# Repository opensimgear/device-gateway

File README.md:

# OpenSimGear device-gateway

## Development status and disclaimer

This project is heavily under development and is not ready for use. Use it entirely at your own risk. To the fullest extent permitted by applicable law, the authors and contributors disclaim all liability for any damage, loss, or other issues arising from its use.

STM32G0B1 USB-to-CAN FD gateway with **USB-C, two parallel 4P4C powered CAN sockets, and a centre-positive 5.5 × 2.1 mm 12 V power socket**. The two CAN sockets continue one linear bus; they are not separate controller channels. The gateway can sit at either end or in the middle of the chain.

## Implemented prototype

- C firmware for `gateway_g0b1cb_v0_1_0`, with USB HID and CDC, a unique MCU-derived USB serial, and active CAN FD at 500 kbit/s arbitration / 2 Mbit/s data.
- Automatic discovery, enrollment and logical route allocation for up to 32 remembered module identities. New input identities append to a persistent ordered controller list; output-only identities retain guarded routes without a HID collection or report ID; enabled offline devices keep neutral HID collections.
- One HID interface with a joystick top-level collection and stable report ID for each enabled module. Each profile supports up to eight 16-bit axes, four hats and 128 buttons. Host/game interpretation of multiple collections still needs physical testing.
- Bounded CAN queues, sequence/lease checks, direct USB input ownership, 250 ms input timeout, 1.5 s presence timeout, and bus-off recovery.
- CRC-protected device visibility and controller order stored in two independent flash pages with a commit marker written last. Automatic batched activation saves an exact generation before USB reconnects; explicit Disable/Enable/Remove retain or forget identities as requested.
- Editable KiCad schematic, PCB, exact-part BOM, local libraries, review and fabrication exports, and a Linux SocketCAN reference peer.

The generic device and gateway now share **Cyphal/CAN**, using generated OpenSimGear
DSDL types and the actual libcanard 5.0 transport. Standard Heartbeat and GetInfo,
CAN node-ID autoconfiguration, transfer-ID deduplication and multi-frame reassembly
run in both firmwares. CAN addresses are separate from the gateway's 32 logical
routes, persistent descriptor order and explicit report IDs. Input acknowledgements still follow actual USB
HID completion. The prior private CAN FD v1/v2 frames are incompatible and rejected.

Cockpit desktop uses the correlated CDC v3 adapter with `canProtocol=3`.

Send `panel-stream\n` on an open CDC connection to opt into unsolicited panel
records. Each record is a complete JSON line between command replies. The
first record has `panelStream: "reset"`. Event records have
`panelStream: "event"`, the module's `moduleId`, its physical `sourceNode`, and
a hexadecimal `payload` containing the Cyphal subject 2007 application bytes.
Wait for a layout and a complete state before applying edges. A
`panelStream: "loss"` record withdraws the named module's state. A reset
withdraws all stream state and can also occur on local queue overflow or
expiration. A new CDC connection requires a new opt-in.
Enrollment runs in the gateway with Cockpit closed. Enabled devices remain neutral
controllers while temporarily offline and appear ghosted in Cockpit. Disable
removes a Windows HID collection while remembering the device and its disabled
choice; repeated announcements and reboot never undo it. Enable appends at the
end. Remove forgets an offline identity; rediscovery enrolls it as new. Removing
published collections warns that remaining game bindings may need updating.

USB exposes only enabled controllers, including their retained offline ghosts.
There is no permanent management collection or unused joystick placeholder;
zero enabled controllers means CDC-only enumeration. Existing controller order,
report IDs and input definitions survive automatic additions, but Windows/game
binding continuity still requires physical qualification, especially transitions
between one and multiple collections. Software resource bounds are explicit,
and excess announcements produce visible capacity diagnostics. Direct device
USB ownership leaves gateway input neutral. The [Pico debug gateway](simulation/pico/README.md)
reuses current gateway/device contracts for eight virtual devices, Cockpit input
controls, physical USB HID, persistent settings and DCS-BIOS panel testing. Older
protocol-1 Pico images retain their compatibility adapter.

Cockpit can claim a module configuration draft, change input mappings/calibration,
and apply or persist its settings over the current identity/session/lease-bound
CAN route. Enabled HID profiles remain frozen until an explicit update-profile
operation; disabled devices remain configurable. Native behavior/journal tests,
actual transport integration, independent gateway/device acceptance and the
STM32 cross-build validate source behavior. Physical USB/CAN acceptance remains
pending. See the [architecture record](https://github.com/opensimgear/opensimgear.github.io/blob/main/src/content/docs/gear/architecture/usb-hid.md)
and [GitHub project](https://github.com/orgs/opensimgear/projects/2).

Cockpit also discovers and invokes device-advertised actions through the guarded
CDC/CAN route. Descriptions, invocations and readable state reuse bounded request/reply
fragments, with separate action dispatch and `targetAction` results. Actions remain
reachable on online disabled controllers and direct-USB input owners after current
lease status arrives. LED setters are volatile and do not claim settings, write flash
or change HID descriptors. The gateway forwards action catalogues without retaining
them in registry storage. Per-endpoint claims/renewal/owned invocation/release
use these same routes and prevent competing clients at the device. Independent
device expiry or route loss applies its validated fallback; tokens remain private.
Output-only modules enroll with `outputOnly:true` and `reportId:null`; Enable
returns `input_not_supported`. Unchanged descriptors activate without USB
reconnection. See the [ownership contract](https://github.com/opensimgear/protocol/blob/main/serial/output-ownership.md). See [milestone 1](https://github.com/opensimgear/cockpit/issues/13)
and the [action contract](https://github.com/opensimgear/protocol/blob/main/serial/device-actions.md).

The same guarded request/reply transport also carries `events state` and
`events read <stream> <after>`, returning request-scoped `targetEvents` JSON.
Devices retain ordered debounced button/encoder transitions in their own bounded
log; the gateway forwards pages independently of HID enablement or direct USB
ownership. Consumers baseline before forwarding new presses and recover from
explicit stream/gap errors. See the [panel event contract](https://github.com/opensimgear/protocol/blob/main/serial/panel-input-events.md).

Radio panels reuse these same routes: display actions declare fitted geometry and
encoding, and event snapshots add maintained/selector metadata plus independent
calibrated axes and availability. The gateway forwards these bounded JSON fields
without storing output state or inferring it from HID. The starter has no fitted
display; native radio frequency/preset/text ports execute the same product callbacks
that a physical display driver supplies. See the [radio simulation](https://github.com/opensimgear/device-template/blob/main/simulation/configs/radio-panel.json).

## Independent simulation

From this repository, launch the native gateway:

```sh
python3 simulation/run.py --identity 0123456789abcdef01234567
```

Start Cockpit normally, then start two or three device processes from
[device-template/simulation](https://github.com/opensimgear/device-template/tree/main/simulation),
using the same gateway identity and separate JSON definitions. Devices may start
before or after the gateway. Cockpit discovers the ordinary gateway endpoint;
it does not start or configure simulation processes. The gateway owns discovery,
automatic enrollment, configuration forwarding and dynamic HID reports. Closing Cockpit
leaves the processes running. See [the simulation guide](simulation/README.md)
for state, diagnostics and the optional [Pico implementation](simulation/pico/README.md).

Run integration tests from this repository alone:

```sh
python3 tests/e2e/run.py --sanitize
python3 tests/e2e/run.py --sanitize --with-cockpit
```

The runner clones and initializes required repositories, builds their components,
and tests three independently configured devices. `--with-cockpit` also clones
Cockpit and tests its normal Rust adapters. Everything stays under this repository’s
ignored `.e2e/`; no sibling checkout or parent workspace setup is required. See the
[E2E guide](tests/e2e/README.md) for source revisions and local development overrides.
Standalone simulation builds and state stay in `.simulation/`.

The native simulation generates production HID descriptors and input reports,
with HID delivery completed inside the process. It does not publish devices to
the host operating system, so simulated controllers do not appear in `hidutil list`.

## Connectors and power

Both sockets use the same four contacts, numbered by the selected manufacturer's drawing:

| Contact | Signal            |
| ------- | ----------------- |
| 1       | Protected BUS_12V |
| 2       | CAN_H             |
| 3       | CAN_L             |
| 4       | GND               |

Use continuity-checked straight-through wiring with CAN_H/L on a qualified twisted pair. Ordinary reversed or coiled handset cords are not qualified CAN cables. Put 120 Ω across contacts 2/3 in a removable endpoint plug at each physical end of the chain; an inline gateway has no termination. A 4P4C jack is commonly called RJ9/RJ10/RJ22 rather than RJ11. This connector choice follows the requested four-position, four-contact standard.

One regulated external 12 V supply feeds each chain through protected gateway injection. USB powers the local gateway electronics and does not energize the chain. The provisional bench budget is **250 mA total for the gateway's 12 V branch and all modules**, at 20–40 °C, with a supply current limit of 0.5 A. The PCB's resettable fuse is not a precision current limiter. Cable resistance, thermal behaviour, short-circuit protection and hot-plug behaviour require measurement. The 32-identity software bound does not establish a 32-module power allowance.

Use one gateway per CAN/power chain. Multiple gateways connect independently to the host by USB; do not join their CAN or powered trunks. CAN and power pass-through are passive and continue through local MCU reset. Historical six-contact module boards have a different pinout and are incompatible with the new four-contact standard.

## Build and review

From `firmware/`, run the native checks without downloading dependencies:

```sh
cmake --preset native
cmake --build --preset native
ctest --preset native
```

For the embedded build, put Arm GNU Embedded tools on PATH and supply USB identifiers you are authorized to use:

```sh
cmake --preset gateway -DOSG_USB_VID=<your-VID> -DOSG_USB_PID=<your-PID>
cmake --build --preset gateway
```

ELF, BIN, HEX and MAP outputs are placed under `.build/gateway/`. No command flashes hardware automatically. See the [firmware guide](firmware/README.md) for exact dependency pins, SWD flashing, recovery and CDC commands. See [CAN peer testing](tools/README.md) for an executable matching module peer.

- [PCB project, pin map and BOM](electronics/boards/gateway/0.1.0/README.md)
- [Fabrication construction](electronics/boards/gateway/0.1.0/FABRICATION.md)
- [Electrical/static validation](electronics/boards/gateway/0.1.0/VALIDATION.md)
- [Firmware validation results](firmware/VALIDATION.md)
- [CAN application framing](firmware/docs/cyphal.md)
- [Registration, HID layout and storage semantics](firmware/docs/core.md)
- [Assembly and enclosure constraints](hardware/README.md)

Static checks and cross-compilation establish source-level behaviour. No gateway PCB has been assembled, flashed or electrically measured; fabrication review and physical USB/CAN/power acceptance remain required. The initial network validation target is up to ten modules and 5 m total cable with typical links below 1 m, subject to the power budget established by measurement.

## Related repositories and licensing

[Protocol](https://github.com/opensimgear/protocol), [firmware-common](https://github.com/opensimgear/firmware-common), [device-template](https://github.com/opensimgear/device-template), [Cockpit](https://github.com/opensimgear/cockpit), and the [website](https://github.com/opensimgear/opensimgear.github.io) own their respective shared definitions and implementations. This gateway uses pinned common firmware dependencies; a checked-in shared Cyphal snapshot tracks the canonical protocol repository.

Copyright © Ivan Gregurić Ortolan. All rights reserved for original OpenSimGear material while licensing is under review. The [temporary licensing policy](LICENSE) defines the current scope for firmware, electronics and other original material. Creative external contributions are suspended during review; [CONTRIBUTING.md](CONTRIBUTING.md) explains the policy for factual bug reports and questions. Included KiCad library data retains its [upstream license](electronics/boards/gateway/0.1.0/LICENSE-KICAD.md), and firmware dependencies retain their upstream licenses and notices. No public USB VID/PID allocation is claimed.

PCB version **0.1.0** stays fixed while pre-live; see [PCB versioning](electronics/VERSIONING.md).

## JLCPCB exports

From this repository root, run `sh tools/bundle-jlcpcb.sh` for the latest numeric board version, or `sh tools/bundle-jlcpcb.sh 0.1.0` for a specific version. Requires KiCad 10 (`kicad-cli`) and Python 3. The script generates a Gerber ZIP plus separate JLCPCB BOM/CPL CSVs in the workspace `.research/jlcpcb/` directory. Use `--output-dir path` to change the destination or `--smd-only` to omit through-hole assembly. See [tool usage](tools/README.md) and the board’s fabrication notes before ordering.

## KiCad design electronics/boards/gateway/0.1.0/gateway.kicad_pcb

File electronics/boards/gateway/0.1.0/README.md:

# Gateway v0.1.0

## Development status and disclaimer

This project is heavily under development and is not ready for use. Use it entirely at your own risk. To the fullest extent permitted by applicable law, the authors and contributors disclaim all liability for any damage, loss, or other issues arising from its use.

Open `gateway.kicad_pro` in **KiCad 10**. This revision develops the gateway around the reviewed STM32G0B1 starter core, adding protected 12 V injection and two physical **4P4C** modular CAN/power sockets. The board is a prototype; no assembly has been measured or fabricated. [Validation](VALIDATION.md) records actual static results and validation limits. [Fabrication](FABRICATION.md), [footprint review](FOOTPRINTS.md), [BOM](bom.csv), [schematic](review/schematic.pdf) and [copper preview](review/pcb.svg) and [1:1 assembly drawings](review/assembly.pdf) accompany the editable CAD.

The connectors are four-position/four-contact jacks, often sold as RJ9/RJ10/RJ22 handset connectors. They are smaller than six-position RJ11/RJ12 sockets. They implement the user's final **4P4C everywhere** requirement. These powered sockets must never connect to telephone equipment. The former six-contact template ecosystem must be migrated before connecting a module; adapters or casual telephone-cord substitutions are not assumed safe.

| Socket / header | Contacts |
| --- | --- |
| J1 USB-C | USB 2.0 device, external 5.1 kΩ Rd on CC1/CC2, no USB PD |
| J2/J3 powered CAN | 1 protected BUS_12V; 2 CAN_H; 3 CAN_L; 4 GND |
| J5 12 V barrel | 5.5 mm OD / 2.1 mm ID mating plug, center positive; sleeve GND; switched sleeve unused |
| J4 SWD | 1 target 3.3 V reference, 2 GND, 3 SWDIO, 4 SWCLK, 5 NRST |
| J6 CAN test | 1 CAN_H, 2 CAN_L, 3 GND; no power output |

Contact numbering comes from the exact manufacturer's drawing and local footprint; see [FOOTPRINTS.md](FOOTPRINTS.md). Qualify a straight-through four-conductor cable whose center pair carries CAN_H/L as a twisted pair. Most handset cords reverse contacts end to end and many are flat, untwisted cable. A reversed cord swaps both power polarity and CAN polarity. Use continuity checks at every contact before energizing any new cable. No hot-plug or cable-current qualification has been established.

J2 and J3 are electrically parallel on a single CAN FD segment. Copper passes CAN and protected trunk power through independently of MCU reset or firmware. Use a linear chain. Fit a removable **120 Ω, 1%, ≥0.25 W** resistor between contacts **2 and 3 only** inside an endpoint plug in the unused gateway port, and a second endpoint plug in the final module's unused port. Remove termination on every intermediate module. There is no permanent PCB terminator; J6 is a bench test connection. Do not form a ring.

The barrel input feeds F2 (350 mA hold / 750 mA trip, 30 V PPTC), D6 SS14 reverse-polarity diode, then D7 SMBJ15A TVS at BUS_12V. Both jacks and the MCU branch receive this protected voltage. F1 (200 mA hold / 30 V) separately protects the MCU branch, followed by D1, the local D5 TVS and RECOM 5 V converter. U6/U7 LM66100 combine regulated bus power and USB VBUS into SYS_5V with TI's Figure 17 continuous-output priority topology: the buck-side status output drives USB-side enable through OR_STATUS, with R6 pulling up to BUCK_5V, followed by the 3.3 V LDO. USB never has a path that generates 12 V. The power-source selection is passive and independent of firmware; leakage, backfeed and source transitions still require measurement. Use one 12 V source per trunk; do not join independently powered gateways.

Use a **current-limited regulated 12 V bench supply, set ≤0.5 A**, and provisionally budget **≤250 mA total** at the barrel input at 20–40°C, including the gateway and all chain devices. The connector's 1.5 A/contact rating does not establish a cable/system current budget. F2's hold rating derates with temperature (300 mA at 40°C and 150 mA at 85°C); a PPTC is a slow fault element, not an accurate electronic current limiter. This prototype has no sustained-overvoltage cutoff. TVS and fuse behaviour under actual faults, wire heating, diode drop and connector temperature must be qualified before extending these limits.

| Firmware signal | MCU pad | LQFP48 pin |
| --- | --- | --- |
| USB D− / D+ | PA11 / PA12 | 33 / 34 |
| USB VBUS presence | PB0, 10 kΩ / 15 kΩ divider | 19 |
| CAN RX / TX | PB8 / PB9, AF3 | 47 / 48 |
| CAN standby, high = standby | PB5, external 10 kΩ pull-up | 44 |
| LED, active high through 1 kΩ | PA5 | 16 |
| SWDIO / SWCLK | PA13 / PA14 | 35 / 36 |
| Reset | PF2-NRST | 10 |

Clocks use internal oscillators. VDD, VDDA, VREF+ and VBAT use 3.3 V; the LQFP48 package internally connects USB supply to VDD. Leave PA11/PA12 remapping disabled and disable UCPD dead-battery pull-downs on unused PA9/PA10. The transceiver is in standby during reset; CAN traffic and chain power continue through the passive connectors. External control headers from the device template are absent.

The four-layer board retains the 65 × 55 mm outline and reviewed USB geometry: 0.2474 mm main track width / 0.1501 mm pair gap above a continuous L2 reference plane. Request the documented JLC04161H-7628 construction, 90 Ω differential ±10%, final geometry approval and coupon/TDR; the calculation is not a measured impedance. See [fabrication instructions](FABRICATION.md). Reproduce static checks and exports with `sh tools/check-and-export.sh 0.1.0` from the repository root after every CAD edit.

`KiCad.kicad_sym` / `KiCad.pretty` retain selected upstream library entries under [KiCad's license](LICENSE-KICAD.md). `OpenSimGear` contains local manufacturer-derived connector, PPTC and other reviewed footprints. Upstream 3D paths require KiCad's model installation; newly authored parts deliberately omit unverified models.

Follow [PCB versioning](../../../VERSIONING.md): this single current design is version **0.1.0**, held fixed until launch.

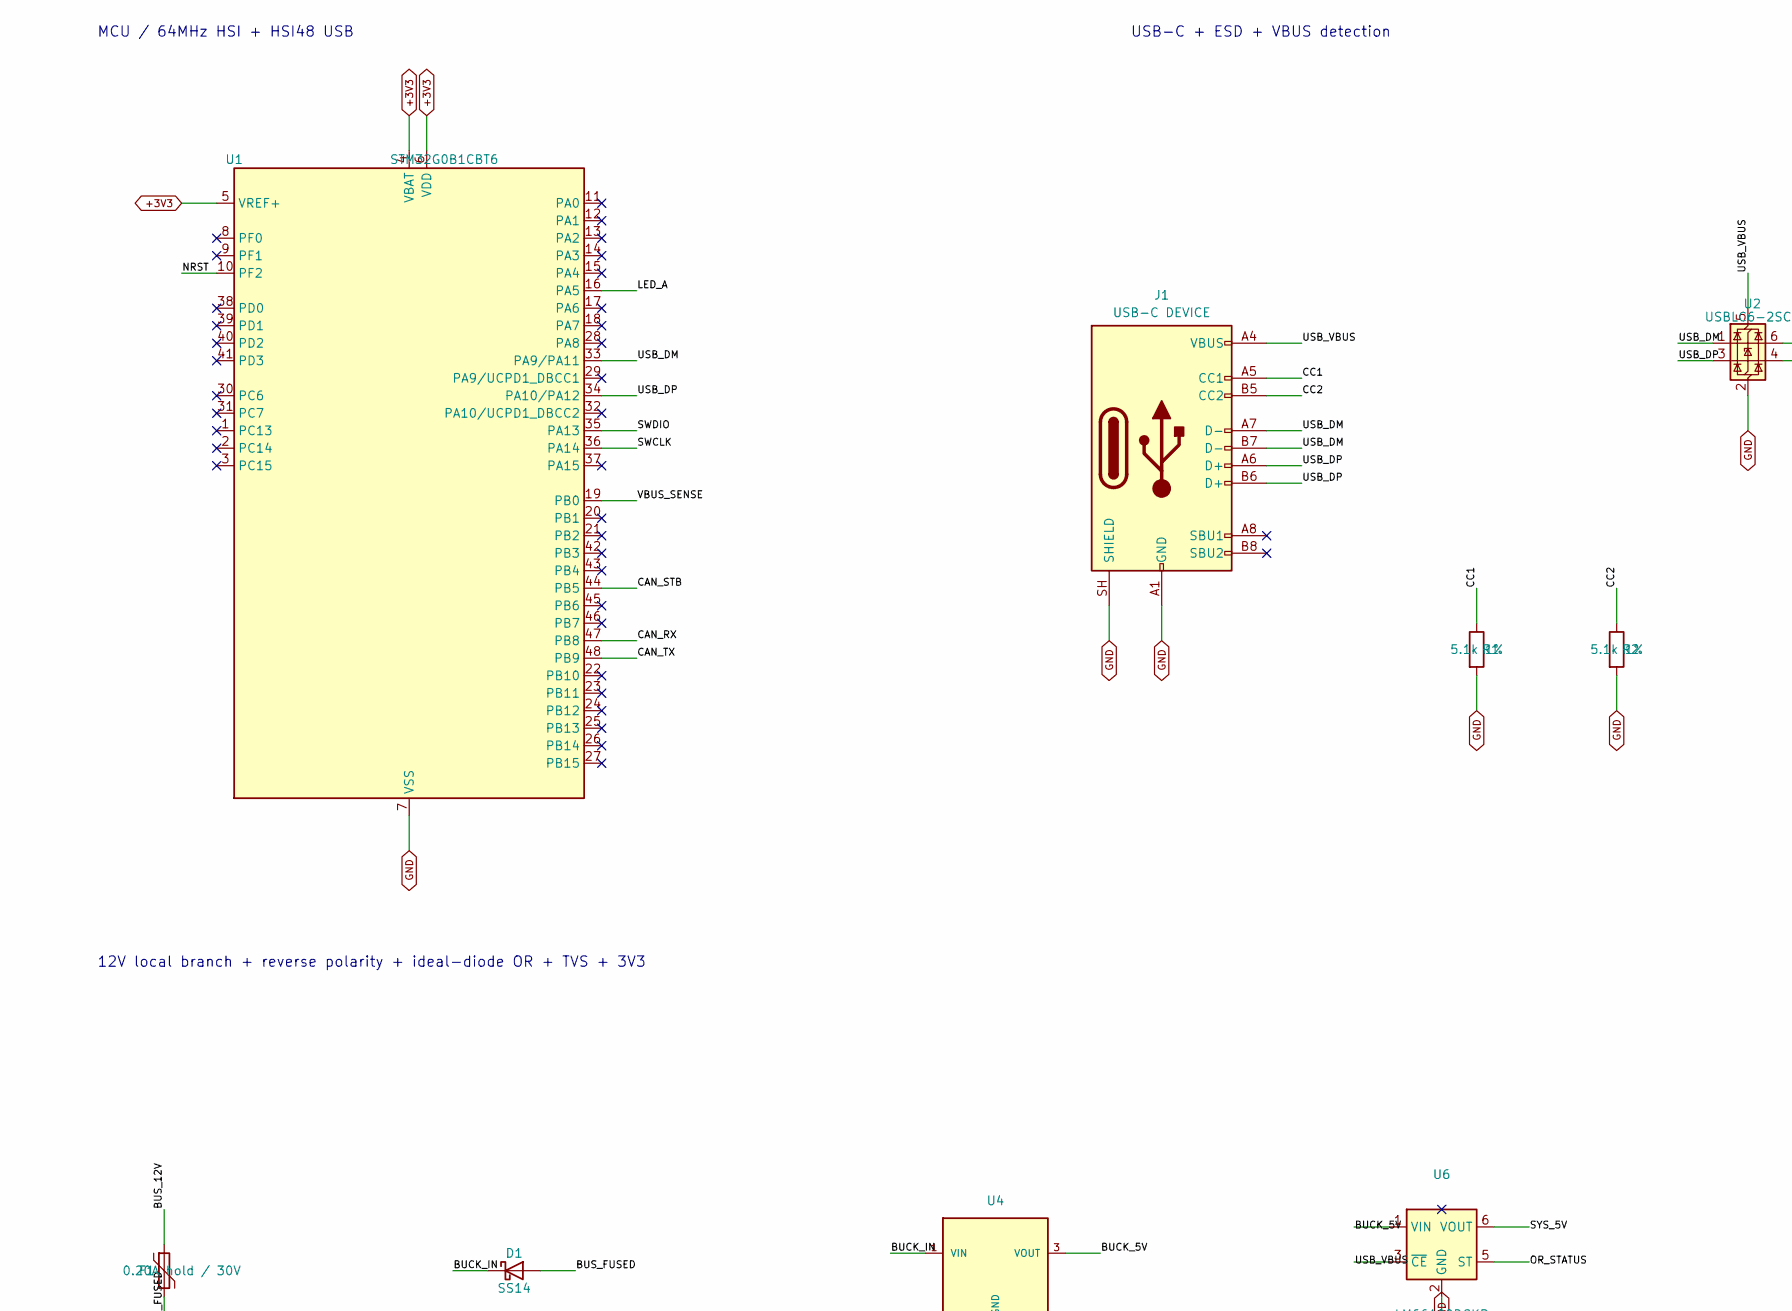
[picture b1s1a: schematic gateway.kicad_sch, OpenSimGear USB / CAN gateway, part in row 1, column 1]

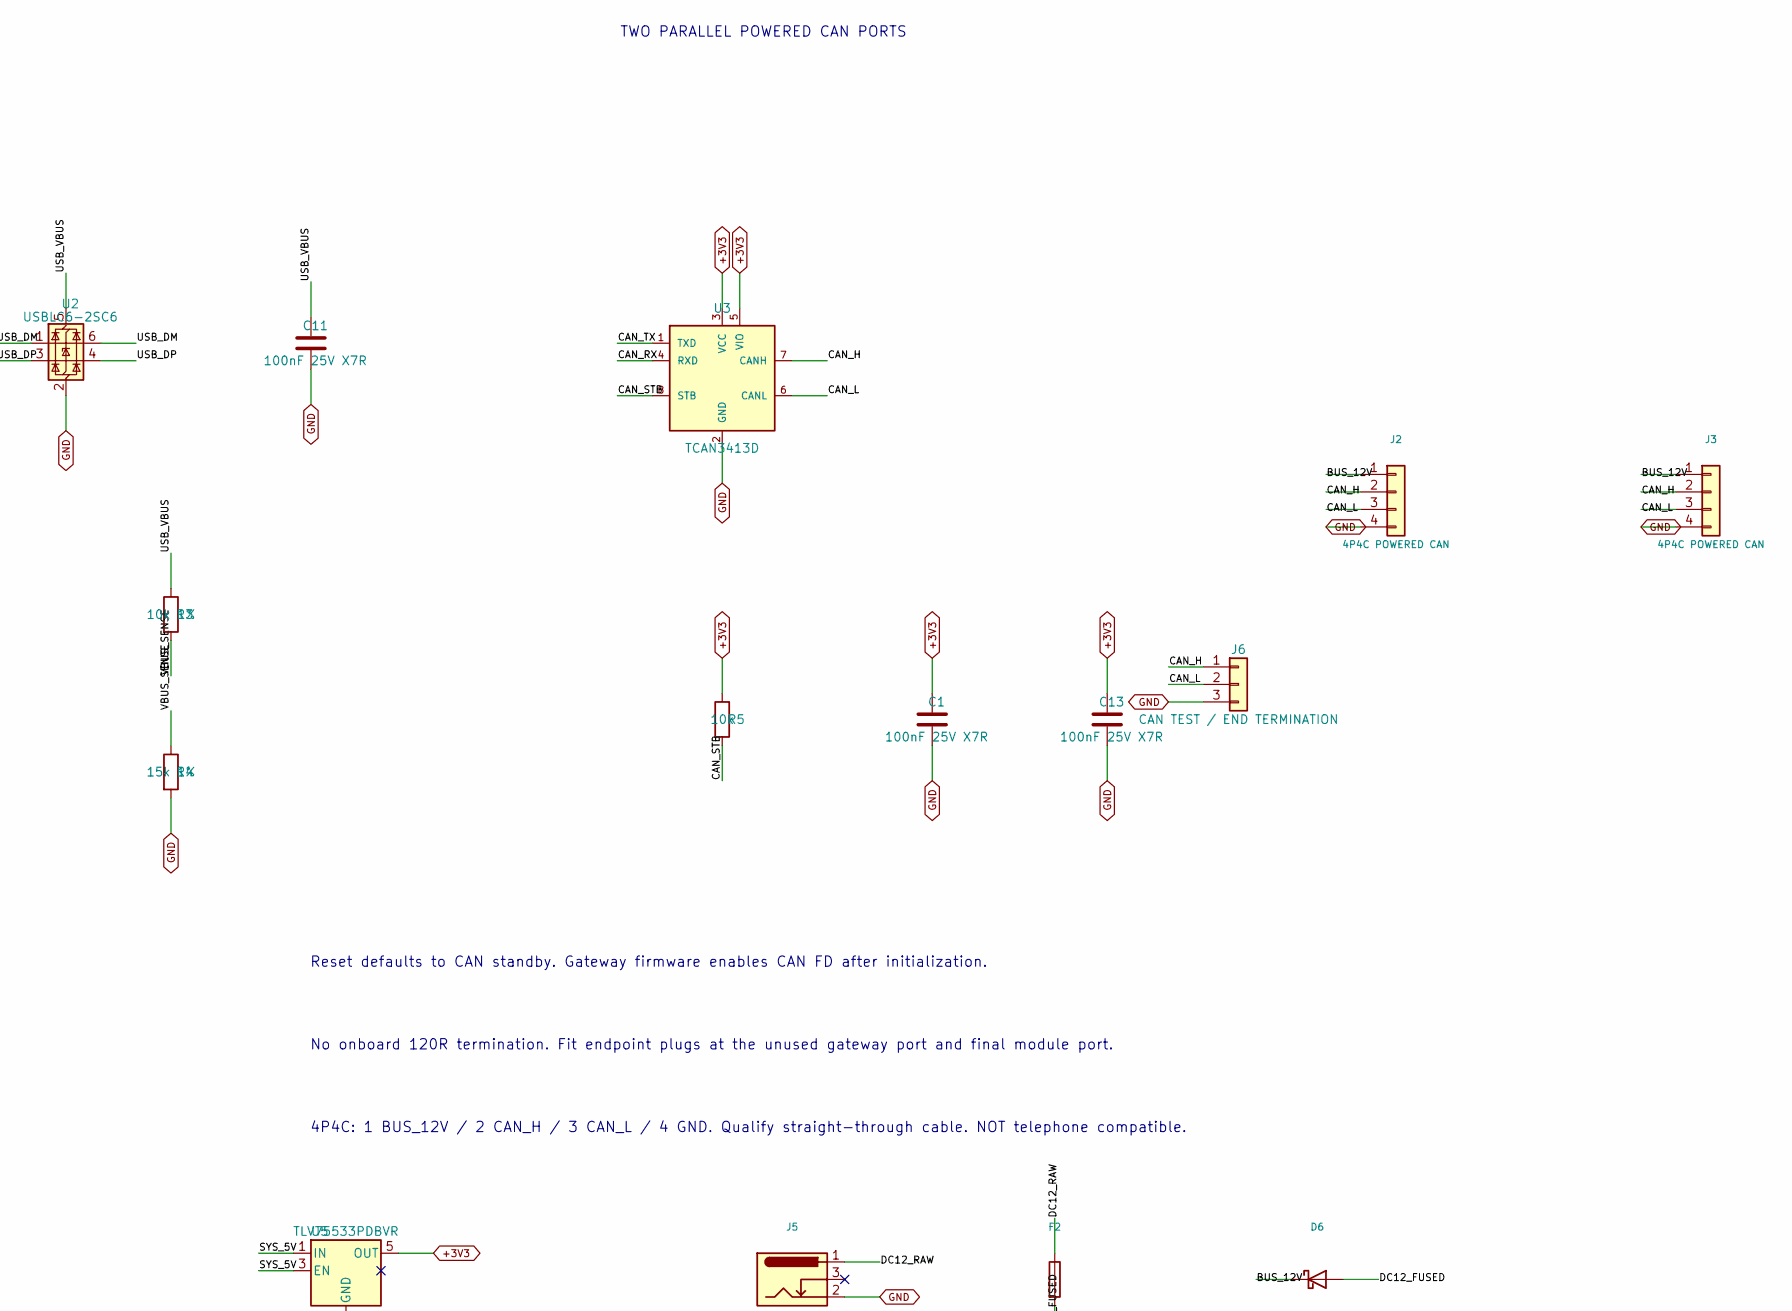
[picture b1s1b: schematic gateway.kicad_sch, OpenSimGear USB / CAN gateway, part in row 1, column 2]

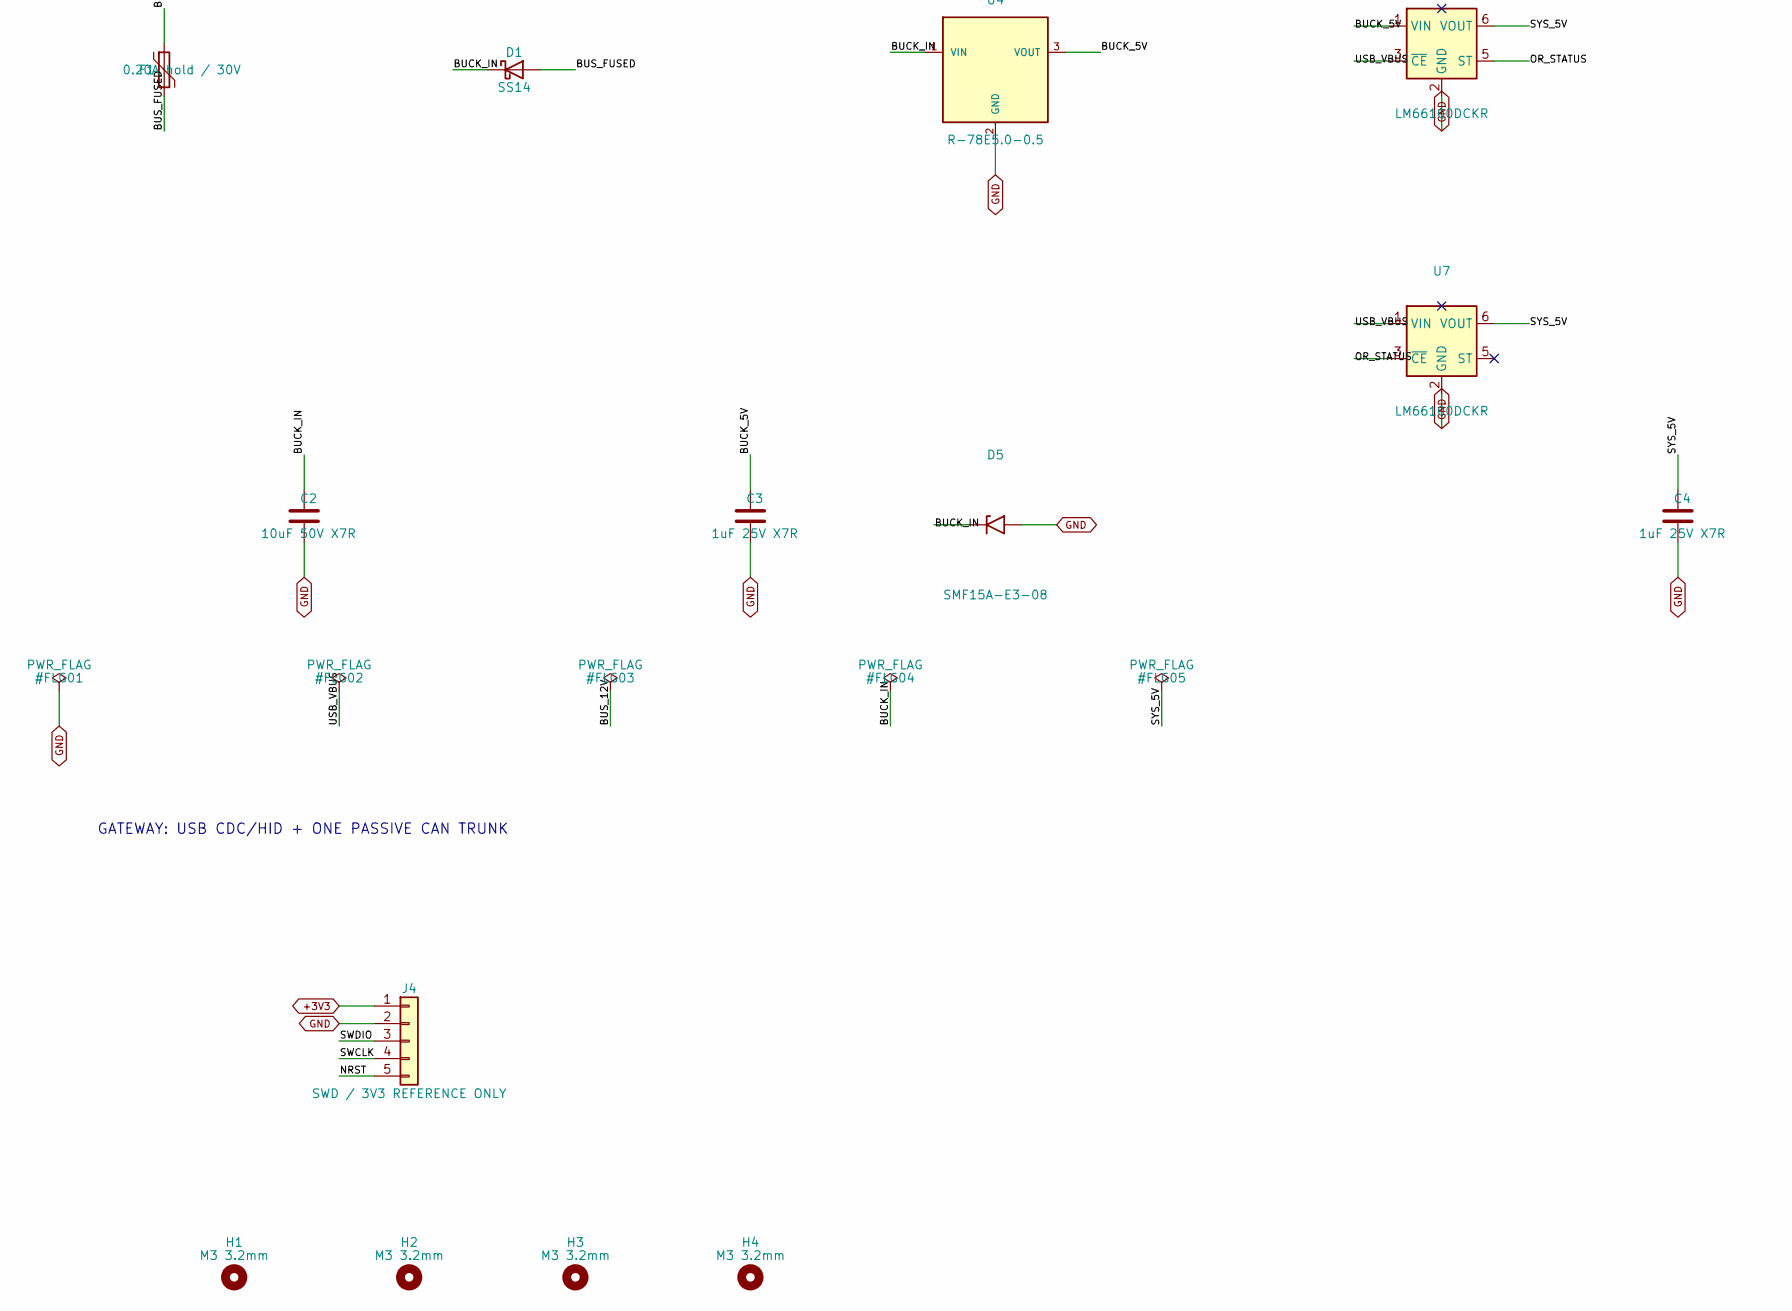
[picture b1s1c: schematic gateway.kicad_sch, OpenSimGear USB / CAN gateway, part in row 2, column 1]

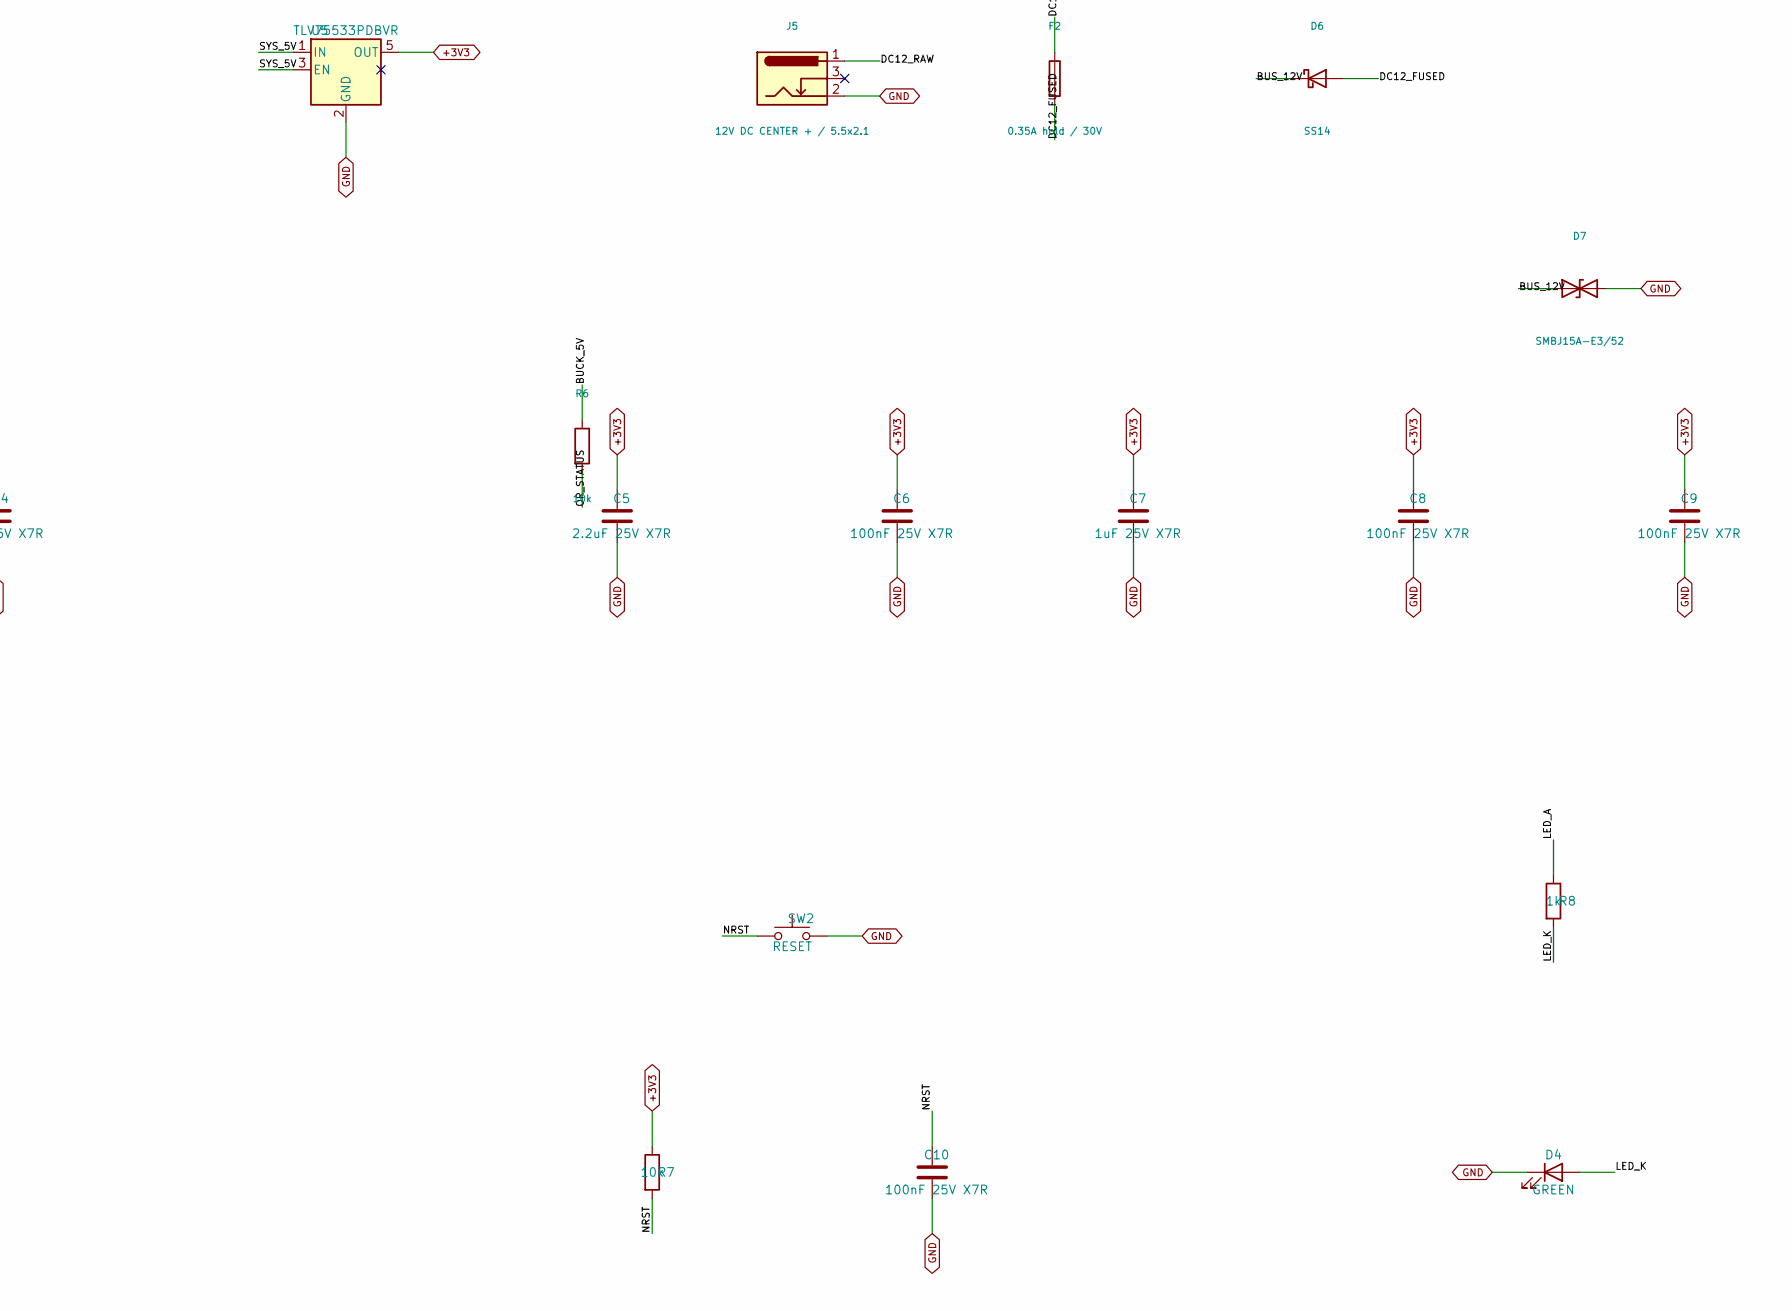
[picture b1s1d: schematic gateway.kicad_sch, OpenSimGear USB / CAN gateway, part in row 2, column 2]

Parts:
C1, C6, C8, C9, C10, C11, C13: 100nF 25V X7R; C_0805_2012Metric; MPN C0805C104K3RACTU
C2: 10uF 50V X7R; C_1210_3225Metric; MPN GRM32ER71H106KA12L
C3, C4, C7: 1uF 25V X7R; C_0805_2012Metric; MPN C2012X7R1E105K125AB
C5: 2.2uF 25V X7R; C_0805_2012Metric; MPN C2012X7R1E225K125AB
D1, D6: SS14; D_SMA; MPN SS14-E3/61T
D4: GREEN; LED_Kingbright_AP2012SGC_0805; MPN AP2012SGC
D5: SMF15A-E3-08; D_SMF; MPN SMF15A-E3-08
D7: SMBJ15A-E3/52; D_SMB; MPN SMBJ15A-E3/52
F1: 0.20A hold / 30V; Fuse_Littelfuse_1206L020-30YR; MPN 1206L020/30YR
F2: 0.35A hold / 30V; Fuse_Littelfuse_1206L035-30WR; MPN 1206L035/30WR
H1, H2, H3, H4: M3 3.2mm; MountingHole_3.2mm_M3
J1: USB-C DEVICE; USB_C_Receptacle_GCT_USB4105-xx-A_16P_TopMnt_Horizontal; MPN USB4105-GF-A
J2, J3: 4P4C POWERED CAN; RJ4P4C_Evercom_5301-4P4C_Horizontal; MPN 5301-4P4C
J4: SWD / 3V3 REFERENCE ONLY; PinHeader_Samtec_TSW-105-07-L-S_P2.54mm_Vertical; MPN TSW-105-07-L-S
J5: 12V DC CENTER + / 5.5x2.1; BarrelJack_SameSky_PJ-102AH_Horizontal; MPN PJ-102AH
J6: CAN TEST / END TERMINATION; PinHeader_Samtec_TSW-103-07-L-S_P2.54mm_Vertical; MPN TSW-103-07-L-S
R1, R2: 5.1k 1%; R_0805_2012Metric; MPN RC0805FR-075K1L
R3: 10k 1%; R_0805_2012Metric; MPN RC0805FR-0710KL
R4: 15k 1%; R_0805_2012Metric; MPN RC0805FR-0715KL
R5, R6, R7: 10k; R_0805_2012Metric; MPN RC0805FR-0710KL
R8: 1k; R_0805_2012Metric; MPN RC0805FR-071KL
SW2: RESET; SW_PUSH_6mm_H4.3mm; MPN B3F-1002-G
U1: STM32G0B1CBT6; LQFP-48_7x7mm_P0.5mm; MPN STM32G0B1CBT6
U2: USBLC6-2SC6; SOT-23-6; MPN USBLC6-2SC6
U3: TCAN3413D; SOIC-8_3.9x4.9mm_P1.27mm; MPN TCAN3413D
U4: R-78E5.0-0.5; Converter_DCDC_RECOM_R-78E-0.5_THT; MPN R-78E5.0-0.5
U5: TLV75533PDBVR; SOT-23-5; MPN TLV75533PDBVR
U6, U7: LM66100DCKR; TI_DCK0006A_SC70-6_LM66100; MPN LM66100DCKR

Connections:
+3V3: C1.1, C5.1, C6.1, C7.1, C8.1, C9.1, C13.1, J4.1, R5.1, R7.1, U1.4 (VBAT), U1.5 (VREF+), U1.6 (VDD), U3.3 (VCC), U3.5 (VIO), U5.5 (OUT)
/BUCK_5V: C3.1, R6.1, U4.3 (VOUT), U6.1 (VIN)
/BUCK_IN: C2.1, D1.1 (K), D5.1 (A1), U4.1 (VIN)
/BUS_12V: D6.1 (K), D7.1 (A1), F1.1, J2.1, J3.1
/BUS_FUSED: D1.2 (A), F1.2
/CAN_H: J2.2, J3.2, J6.1, U3.7 (CANH)
/CAN_L: J2.3, J3.3, J6.2, U3.6 (CANL)
/CAN_RX: U1.47 (PB8), U3.4 (RXD)
/CAN_STB: R5.2, U1.44 (PB5), U3.8 (STB)
/CAN_TX: U1.48 (PB9), U3.1 (TXD)
/CC1: J1.A5 (CC1), R1.1
/CC2: J1.B5 (CC2), R2.1
/DC12_FUSED: D6.2 (A), F2.2
/DC12_RAW: F2.1, J5.1
/LED_A: R8.1, U1.16 (PA5)
/LED_K: D4.2 (A), R8.2
/NRST: C10.1, J4.5, R7.2, SW2.1, U1.10 (PF2)
/OR_STATUS: R6.2, U6.5 (ST), U7.3 (~CE)
/SWCLK: J4.4, U1.36 (PA14)
/SWDIO: J4.3, U1.35 (PA13)
/SYS_5V: C4.1, U5.1 (IN), U5.3 (EN), U6.6 (VOUT), U7.6 (VOUT)
/USB_DM: J1.A7 (D-), J1.B7 (D-), U1.33 (PA9/PA11), U2.1 (I/O1), U2.6 (I/O1)
/USB_DP: J1.A6 (D+), J1.B6 (D+), U1.34 (PA10/PA12), U2.3 (I/O2), U2.4 (I/O2)
/USB_VBUS: C11.1, J1.A4 (VBUS), J1.A9 (VBUS), J1.B4 (VBUS), J1.B9 (VBUS), R3.1, U2.5 (VBUS), U6.3 (~CE), U7.1 (VIN)
/VBUS_SENSE: R3.2, R4.1, U1.19 (PB0)
GND: C1.2, C2.2, C3.2, C4.2, C5.2, C6.2, C7.2, C8.2, C9.2, C10.2, C11.2, C13.2, D4.1 (K), D5.2 (A2), D7.2 (A2), J1.A1 (GND), J1.A12 (GND), J1.B1 (GND), J1.B12 (GND), J1.SH (SHIELD), J2.4, J3.4, J4.2, J5.2, J6.3, R1.2, R2.2, R4.2, SW2.2, U1.7 (VSS), U2.2 (GND), U3.2 (GND), U4.2 (GND), U5.2 (GND), U6.2 (GND), U7.2 (GND)

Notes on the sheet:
12V local branch + reverse polarity + ideal-diode OR + TVS + 3V3
No onboard 120R termination. Fit endpoint plugs at the unused gateway port and final module port.
MCU / 64MHz HSI + HSI48 USB
TWO PARALLEL POWERED CAN PORTS
4P4C: 1 BUS_12V / 2 CAN_H / 3 CAN_L / 4 GND. Qualify straight-through cable. NOT telephone compatible.
Reset defaults to CAN standby. Gateway firmware enables CAN FD after initialization.
USB-C + ESD + VBUS detection
GATEWAY: USB CDC/HID + ONE PASSIVE CAN TRUNK

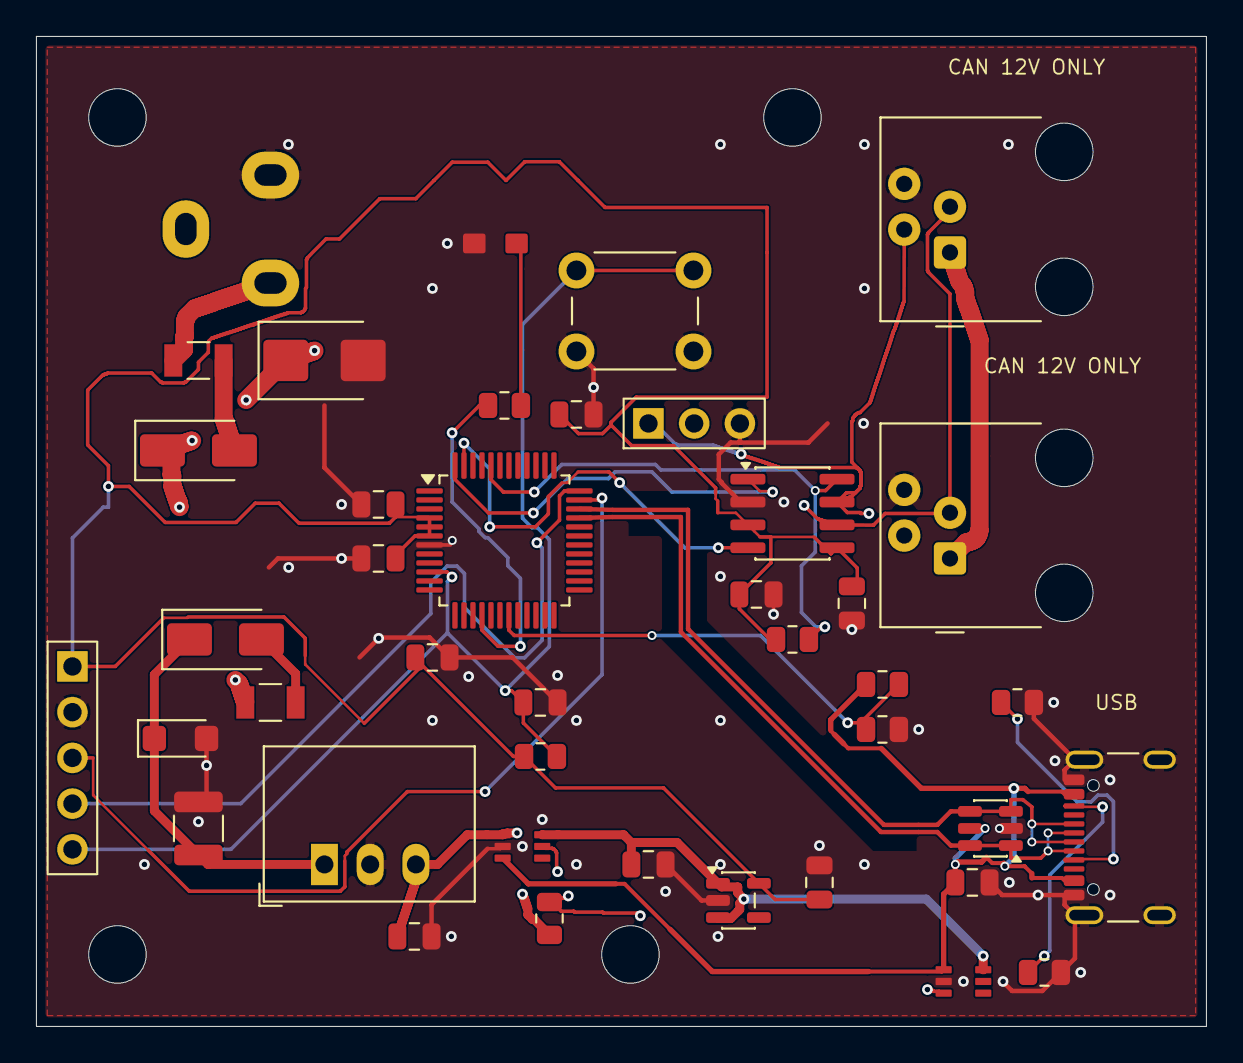
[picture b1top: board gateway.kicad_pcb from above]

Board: 4 copper layers, 65.0 x 55.0 mm, 45 parts (0 on the bottom side), 26 nets.

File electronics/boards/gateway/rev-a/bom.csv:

"Reference","Value","Manufacturer part","Footprint","Datasheet"
"C1","100nF 25V X7R","C0805C104K3RACTU","KiCad:C_0805_2012Metric","https://content.kemet.com/datasheets/KEM_C1002_X7R_SMD.pdf"
"C2","10uF 50V X7R","GRM32ER71H106KA12L","KiCad:C_1210_3225Metric","https://search.murata.co.jp/Ceramy/image/img/A01X/G101/ENG/G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"
"C3","1uF 25V X7R","C2012X7R1E105K125AB","KiCad:C_0805_2012Metric","https://product.tdk.com/en/search/capacitor/ceramic/mlcc/inf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"
"C4","1uF 25V X7R","C2012X7R1E105K125AB","KiCad:C_0805_2012Metric","https://product.tdk.com/en/search/capacitor/ceramic/mlcc/inf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"
"C5","2.2uF 25V X7R","C2012X7R1E225K125AB","KiCad:C_0805_2012Metric","https://product.tdk.com/en/search/capacitor/ceramic/mlcc/inf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"
"C6","100nF 25V X7R","C0805C104K3RACTU","KiCad:C_0805_2012Metric","https://content.kemet.com/datasheets/KEM_C1002_X7R_SMD.pdf"
"C7","1uF 25V X7R","C2012X7R1E105K125AB","KiCad:C_0805_2012Metric","https://product.tdk.com/en/search/capacitor/ceramic/mlcc/inf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"
"C8","100nF 25V X7R","C0805C104K3RACTU","KiCad:C_0805_2012Metric","https://content.kemet.com/datasheets/KEM_C1002_X7R_SMD.pdf"
"C9","100nF 25V X7R","C0805C104K3RACTU","KiCad:C_0805_2012Metric","https://content.kemet.com/datasheets/KEM_C1002_X7R_SMD.pdf"
"C10","100nF 25V X7R","C0805C104K3RACTU","KiCad:C_0805_2012Metric","https://content.kemet.com/datasheets/KEM_C1002_X7R_SMD.pdf"
"C11","100nF 25V X7R","C0805C104K3RACTU","KiCad:C_0805_2012Metric","https://content.kemet.com/datasheets/KEM_C1002_X7R_SMD.pdf"
"C13","100nF 25V X7R","C0805C104K3RACTU","KiCad:C_0805_2012Metric","https://content.kemet.com/datasheets/KEM_C1002_X7R_SMD.pdf"
"D1","SS14","SS14-E3/61T","KiCad:D_SMA","https://www.vishay.com/docs/88746/ss12.pdf"
"D4","GREEN","AP2012SGC","OpenSimGear:LED_Kingbright_AP2012SGC_0805","https://www.kingbrightusa.com/images/catalog/SPEC/AP2012SGC.pdf"
"D5","SMF15A-E3-08","SMF15A-E3-08","KiCad:D_SMF","https://www.vishay.com/docs/85881/smf5v0atosmf58a.pdf"
"D6","SS14","SS14-E3/61T","KiCad:D_SMA","https://www.vishay.com/docs/88746/ss12.pdf"
"D7","SMBJ15A-E3/52","SMBJ15A-E3/52","KiCad:D_SMB","https://www.vishay.com/docs/88392/smbj.pdf"
"F1","0.20A hold / 30V","1206L020/30YR","OpenSimGear:Fuse_Littelfuse_1206L020-30YR","https://www.littelfuse.com/assetdocs/littelfuse-ptc-1206l-da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"
"F2","0.35A hold / 30V","1206L035/30WR","OpenSimGear:Fuse_Littelfuse_1206L035-30WR","https://www.littelfuse.com/assetdocs/littelfuse-ptc-1206l-da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"
"H1","M3 3.2mm","","KiCad:MountingHole_3.2mm_M3",""
"H2","M3 3.2mm","","KiCad:MountingHole_3.2mm_M3",""
"H3","M3 3.2mm","","KiCad:MountingHole_3.2mm_M3",""
"H4","M3 3.2mm","","KiCad:MountingHole_3.2mm_M3",""
"J1","USB-C DEVICE","USB4105-GF-A","KiCad:USB_C_Receptacle_GCT_USB4105-xx-A_16P_TopMnt_Horizontal","https://gct.co/files/drawings/usb4105.pdf"
"J2","4P4C POWERED CAN","5301-4P4C","OpenSimGear:RJ4P4C_Evercom_5301-4P4C_Horizontal","https://jlcpcb.com/partdetail/EVERCOM-53014P4C/C3097715"
"J3","4P4C POWERED CAN","5301-4P4C","OpenSimGear:RJ4P4C_Evercom_5301-4P4C_Horizontal","https://jlcpcb.com/partdetail/EVERCOM-53014P4C/C3097715"
"J4","SWD / 3V3 REFERENCE ONLY","TSW-105-07-L-S","OpenSimGear:PinHeader_Samtec_TSW-105-07-L-S_P2.54mm_Vertical","https://suddendocs.samtec.com/prints/tsw-xxx-xx-x-x-xx-xxx-f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"
"J5","12V DC CENTER + / 5.5x2.1","PJ-102AH","OpenSimGear:BarrelJack_SameSky_PJ-102AH_Horizontal","https://www.sameskydevices.com/product/resource/pj-102ah.pdf"
"J6","CAN TEST / END TERMINATION","TSW-103-07-L-S","OpenSimGear:PinHeader_Samtec_TSW-103-07-L-S_P2.54mm_Vertical","https://suddendocs.samtec.com/prints/tsw-xxx-xx-x-x-xx-xxx-f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"
"R1","5.1k 1%","RC0805FR-075K1L","KiCad:R_0805_2012Metric","https://www.yageogroup.com/component-documentation/download/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"
"R2","5.1k 1%","RC0805FR-075K1L","KiCad:R_0805_2012Metric","https://www.yageogroup.com/component-documentation/download/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"
"R3","10k 1%","RC0805FR-0710KL","KiCad:R_0805_2012Metric","https://www.yageogroup.com/component-documentation/download/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"
"R4","15k 1%","RC0805FR-0715KL","KiCad:R_0805_2012Metric","https://www.yageogroup.com/component-documentation/download/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"
"R5","10k","RC0805FR-0710KL","KiCad:R_0805_2012Metric","https://www.yageogroup.com/component-documentation/download/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"
"R6","10k","RC0805FR-0710KL","KiCad:R_0805_2012Metric","https://www.yageo.com/upload/media/product/productsearch/dat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"
"R7","10k","RC0805FR-0710KL","KiCad:R_0805_2012Metric","https://www.yageogroup.com/component-documentation/download/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"
"R8","1k","RC0805FR-071KL","KiCad:R_0805_2012Metric","https://www.yageogroup.com/component-documentation/download/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"
"SW2","RESET","B3F-1002-G","KiCad:SW_PUSH_6mm_H4.3mm","https://omronfs.omron.com/en_US/ecb/products/pdf/en-b3f.pdf"
"U1","STM32G0B1CBT6","STM32G0B1CBT6","KiCad:LQFP-48_7x7mm_P0.5mm","https://www.st.com/resource/en/datasheet/stm32g0b1cb.pdf"
"U2","USBLC6-2SC6","USBLC6-2SC6","KiCad:SOT-23-6","https://www.st.com/resource/en/datasheet/usblc6-2.pdf"
"U3","TCAN3413D","TCAN3413D","KiCad:SOIC-8_3.9x4.9mm_P1.27mm","https://www.ti.com/lit/ds/symlink/tcan3413.pdf"
"U4","R-78E5.0-0.5","R-78E5.0-0.5","KiCad:Converter_DCDC_RECOM_R-78E-0.5_THT","https://recom-power.com/pdf/Innoline/R-78E-0.5.pdf"
"U5","TLV75533PDBVR","TLV75533PDBVR","KiCad:SOT-23-5","https://www.ti.com/lit/ds/symlink/tlv755p.pdf"
"U6","LM66100DCKR","LM66100DCKR","OpenSimGear:TI_DCK0006A_SC70-6_LM66100","https://www.ti.com/lit/ds/symlink/lm66100.pdf"
"U7","LM66100DCKR","LM66100DCKR","OpenSimGear:TI_DCK0006A_SC70-6_LM66100","https://www.ti.com/lit/ds/symlink/lm66100.pdf"
